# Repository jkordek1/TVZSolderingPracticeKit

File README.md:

# TVZSolderingPracticeKit

## About

This project is a custom-designed printed circuit board (PCB) developed as an educational tool to help students practice and develop through-hole device (THD) soldering skills. The board integrates simple but functional electronic circuits, centered around the NE555 timer IC, to provide hands-on learning in both soldering and basic circuit operation.

## Functional Overview:

Powered with 9V battery via barrel jack and adapter.

NE555 Piano Buzzer Circuit:
- Based on the NE555 timer configured in astable mode.
- Drives a buzzer to generate audible tones, simulating a simple piano key.

Charge/Discharge with LED Indicators:
- A basic RC charge/discharge circuit is included to illustrate capacitor behavior.
- LEDs serve as visual indicators for charging and discharging states.

Dummy Passive Component Sections:
- Includes extra resistors, pin headers and sockets with no critical function—used purely for soldering practice.
- These sections allow repeated practice without impacting circuit operation.

High-Current Trace Design:
- Selected traces are widened to demonstrate PCB design practices for handling higher currents.
- Offers insight into power and thermal considerations in PCB design.

Design considerations:
- Clearly Labeled Silkscreen: Component values and orientation are printed to assist students during assembly.
- Educational Layout: Segmented functional blocks help isolate and explain circuit behavior.

## Fabrication layer

For PCB assembly, use the Fabrication.html file, which includes an easy-to-use Bill of Materials (BOM) with checkmarks. This file can be opened in any web browser.

## Bill of materials (BOM)

| Reference                       | Value             | Qty | TME Part Number    |
|---------------------------------|-------------------|-----|--------------------|
| BZ1                             | LD-BZEN-1205      | 1   | LD-BZEN-1205       |
| C1                              | 100n              | 1   | C320C104K5R5TA7317 |
| C2                              | 470u / 50V        | 1   | EEUFR1E471         |
| D1                              | SR150-DC          | 1   | SR150-DC           |
| D2                              | RED               | 1   | 1383-2SURD/S530-A3 |
| D3                              | YELLOW            | 1   | 1383UYD/S530-A3    |
| D4                              | GREEN             | 1   | 1383SYGD/S530-E2   |
| D5                              | WHITE             | 1   | INL-5AW30          |
| J1                              | Barrel Jack       | 1   | DCJ250-10-A-K1-K   |
| J2                              | Conn_01x05_Pin    | 1   | PH1RB-40-UA        |
| J3                              | Conn_01x05_Socket | 1   | ZL262-5SG          |
| J4,J5                           | Conn_01x03_Pin    | 2   | ZL201-03G          |
| J6                              | JUMPER-H/R        | 1   | JUMPER-H/R         |
| J7                              | JUMPER-H/B        | 1   | JUMPER-H/B         |
| R1                              | 1k5               | 1   | 1/4W1.5K           |
| R2                              | 1k3               | 1   | 1/4W1.3K           |
| R3                              | 620               | 1   | 1/4W620R           |
| R4                              | 1k1               | 1   | 1/4W1.1K           |
| R5,R9                           | 1k                | 2   | 1/4W1.0K           |
| R6                              | 910               | 1   | 1/4W910R           |
| R7                              | 390               | 1   | CF1/4W-390R        |
| R8                              | 6k2               | 1   | 1/4W6.2K           |
| R10                             | 4k7               | 1   | 1/4W4.7K           |
| R11,R15                         | 2k2               | 2   | 1/4W2.2K           |
| R12,R13,R14                     | 2k2               | 3   | 1/4W2.2K           |
| RV1                             | 10k               | 1   | RK09K1130AH1       |
| SW1,SW2,SW3,SW4,SW5,SW6,SW7,SW8 | SW_Push           | 8   | TACT-64K-F         |
| SW10                            | POWER             | 1   | OS102011MS2QN1     |
| SW11                            | C/D               | 1   | OS102011MS2QN1     |
| U1                              | NE555P            | 1   | NE555P             |
| U2                              | ~                 | 1   | ICVT-8P            |
| U3                              | ~                 | 1   | BAT-6F22L/U-SH     |
| U4,U5,U6,U7                     | ~                 | 4   | B2.5X5/BN2724      |
| U8,U9,U10,U11                   | ~                 | 4   | B3/BN116           |

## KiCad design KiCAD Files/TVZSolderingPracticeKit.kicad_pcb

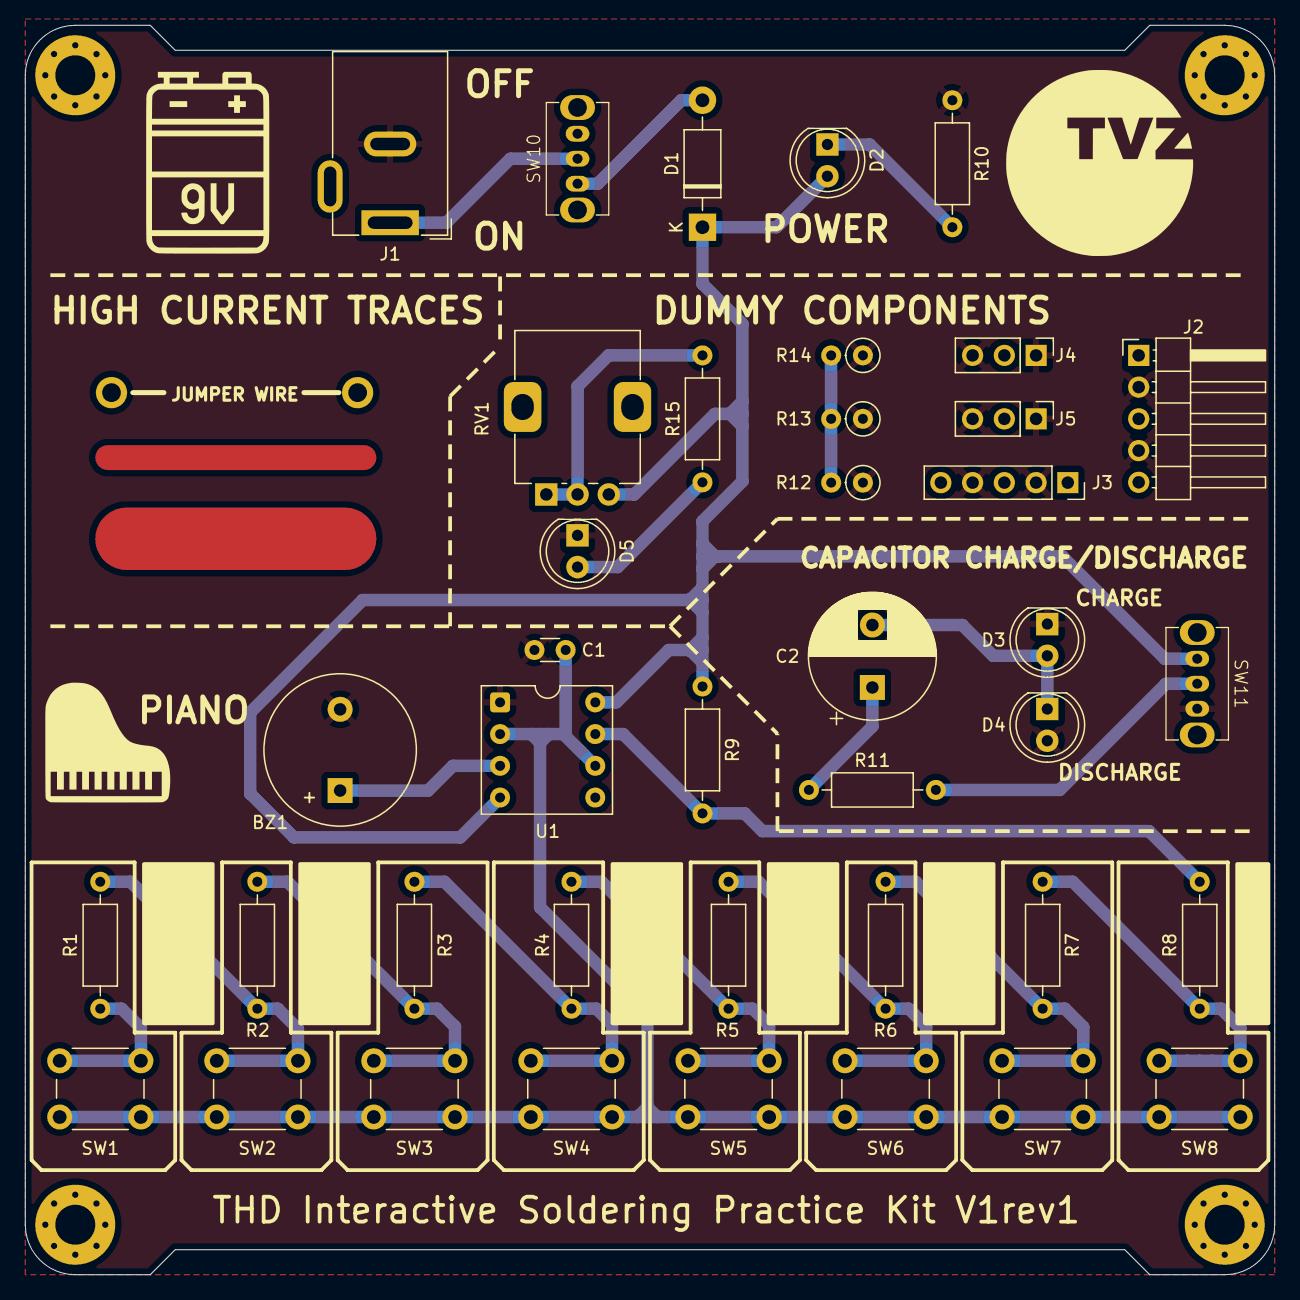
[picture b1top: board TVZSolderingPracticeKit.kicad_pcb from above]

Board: 2 copper layers, 100.0 x 100.0 mm, 46 parts (0 on the bottom side), 22 nets.

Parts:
BZ1: LD-BZEN-1205
C1: 100n; C_Disc_D3.0mm_W1.6mm_P2.50mm
C2: 470u / 50V; CP_Radial_D10.0mm_P5.00mm
D1: SR150-DC; D_DO-41_SOD81_P10.16mm_Horizontal
D2: RED; LED_D5.0mm
D3: YELLOW; LED_D5.0mm
D4: GREEN; LED_D5.0mm
D5: WHITE; LED_D5.0mm
H1, H2, H3, H4: MountingHole_Pad; MountingHole_3.2mm_M3_Pad_Via
J1: Barrel Jack; DCJ250-10-A-K1-K
J2: Conn_01x05_Pin; PinHeader_1x05_P2.54mm_Horizontal
J3: Conn_01x05_Socket; PinSocket_1x05_P2.54mm_Vertical
J4, J5: Conn_01x03_Pin; PinHeader_1x03_P2.54mm_Vertical
R1: 1k5; R_Axial_DIN0207_L6.3mm_D2.5mm_P10.16mm_Horizontal
R2: 1k3; R_Axial_DIN0207_L6.3mm_D2.5mm_P10.16mm_Horizontal
R3: 620; R_Axial_DIN0207_L6.3mm_D2.5mm_P10.16mm_Horizontal
R4: 1k1; R_Axial_DIN0207_L6.3mm_D2.5mm_P10.16mm_Horizontal
R5, R9: 1k; R_Axial_DIN0207_L6.3mm_D2.5mm_P10.16mm_Horizontal
R6: 910; R_Axial_DIN0207_L6.3mm_D2.5mm_P10.16mm_Horizontal
R7: 390; R_Axial_DIN0207_L6.3mm_D2.5mm_P10.16mm_Horizontal
R8: 6k2; R_Axial_DIN0207_L6.3mm_D2.5mm_P10.16mm_Horizontal
R10: 4k7; R_Axial_DIN0207_L6.3mm_D2.5mm_P10.16mm_Horizontal
R11, R15: 2k2; R_Axial_DIN0207_L6.3mm_D2.5mm_P10.16mm_Horizontal
R12, R13, R14: 2k2; R_Axial_DIN0207_L6.3mm_D2.5mm_P2.54mm_Vertical
RV1: 10k; RK09K1130AH1
SW1, SW2, SW3, SW4, SW5, SW6, SW7, SW8: SW_Push; SW_PUSH_6mm_H4.3mm
SW10: POWER; OS102011MS2QN1
SW11: C/D; OS102011MS2QN1
TP1, TP2: TestPoint; Wire
U1: NE555P; DIP-8_W7.62mm-socket

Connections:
GND1: BZ1.2 (-), C1.2, D3.1 (K), D4.2 (A), D5.1 (K), J1.2, J2.2, J2.4, J3.2, J3.4, J4.1, J4.3, J5.1, J5.3, R10.1, R12.1, R13.1, R14.1, SW11.3 (C), U1.1 (GND)
unnamed: BZ1.1 (+), U1.3 (Q)
unnamed: C2.1, R11.1
unnamed: D1.2 (A), SW10.1 (A)
unnamed: D2.1 (K), R10.2
unnamed: C2.2, D3.2 (A), D4.1 (K)
unnamed: D5.2 (A), R15.1
unnamed: R1.1, R2.2, SW2.1
unnamed: R1.2, SW1.1
unnamed: R2.1, R3.2, SW3.1
unnamed: R3.1, R4.2, SW4.1
unnamed: R4.1, R5.2, SW5.1
unnamed: R5.1, R6.2, SW6.1
unnamed: R6.1, R7.2, SW7.1
unnamed: R7.1, R8.2, SW8.1
unnamed: R12.2, R13.2, R14.2
unnamed: R15.2, RV1.1, RV1.2
unnamed: J1.1, SW10.2 (B)
unnamed: R11.2, SW11.2 (B)
unnamed: R8.1, R9.1, U1.7 (DIS)
unnamed: C1.1, SW1.2, SW2.2, SW3.2, SW4.2, SW5.2, SW6.2, SW7.2, SW8.2, U1.2 (TR), U1.6 (THR)
VDD: D1.1 (K), D2.2 (A), R9.2, RV1.3, SW11.1 (A), U1.4 (R), U1.8 (VCC)

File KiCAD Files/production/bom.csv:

Designator,Footprint,Quantity,Value,LCSC Part #
BZ1,LD-BZEN-1205,1,LD-BZEN-1205,
C1,C_Disc_D3.0mm_W1.6mm_P2.50mm,1,100n,
C2,CP_Radial_D10.0mm_P5.00mm,1,470u / 50V,
D1,D_DO-41_SOD81_P10.16mm_Horizontal,1,SR150-DC,
D2,LED_D5.0mm,1,RED,
D3,LED_D5.0mm,1,YELLOW,
D4,LED_D5.0mm,1,GREEN,
D5,LED_D5.0mm,1,WHITE,
J1,DCJ250-10-A-K1-K,1,Barrel Jack,
J2,PinHeader_1x05_P2.54mm_Horizontal,1,Conn_01x05_Pin,
J3,PinSocket_1x05_P2.54mm_Vertical,1,Conn_01x05_Socket,
"J4, J5",PinHeader_1x03_P2.54mm_Vertical,2,Conn_01x03_Pin,
R1,R_Axial_DIN0207_L6.3mm_D2.5mm_P10.16mm_Horizontal,1,1k5,
R10,R_Axial_DIN0207_L6.3mm_D2.5mm_P10.16mm_Horizontal,1,4k7,
"R11, R15",R_Axial_DIN0207_L6.3mm_D2.5mm_P10.16mm_Horizontal,2,2k2,
"R12, R13, R14",R_Axial_DIN0207_L6.3mm_D2.5mm_P2.54mm_Vertical,3,2k2,
R2,R_Axial_DIN0207_L6.3mm_D2.5mm_P10.16mm_Horizontal,1,1k3,
R3,R_Axial_DIN0207_L6.3mm_D2.5mm_P10.16mm_Horizontal,1,620,
R4,R_Axial_DIN0207_L6.3mm_D2.5mm_P10.16mm_Horizontal,1,1k1,
"R5, R9",R_Axial_DIN0207_L6.3mm_D2.5mm_P10.16mm_Horizontal,2,1k,
R6,R_Axial_DIN0207_L6.3mm_D2.5mm_P10.16mm_Horizontal,1,910,
R7,R_Axial_DIN0207_L6.3mm_D2.5mm_P10.16mm_Horizontal,1,390,
R8,R_Axial_DIN0207_L6.3mm_D2.5mm_P10.16mm_Horizontal,1,6k2,
RV1,RK09K1130AH1,1,10k,
"SW1, SW2, SW3, SW4, SW5, SW6, SW7, SW8",SW_PUSH_6mm_H4.3mm,8,SW_Push,
SW10,OS102011MS2QN1,1,POWER,
SW11,OS102011MS2QN1,1,C/D,
U1,DIP-8_W7.62mm-socket,1,NE555P,

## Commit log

2025-06-09 Project created
2025-07-02 Move bottom silk
